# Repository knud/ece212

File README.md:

# ece212
decoder to 8x8 LED matrix

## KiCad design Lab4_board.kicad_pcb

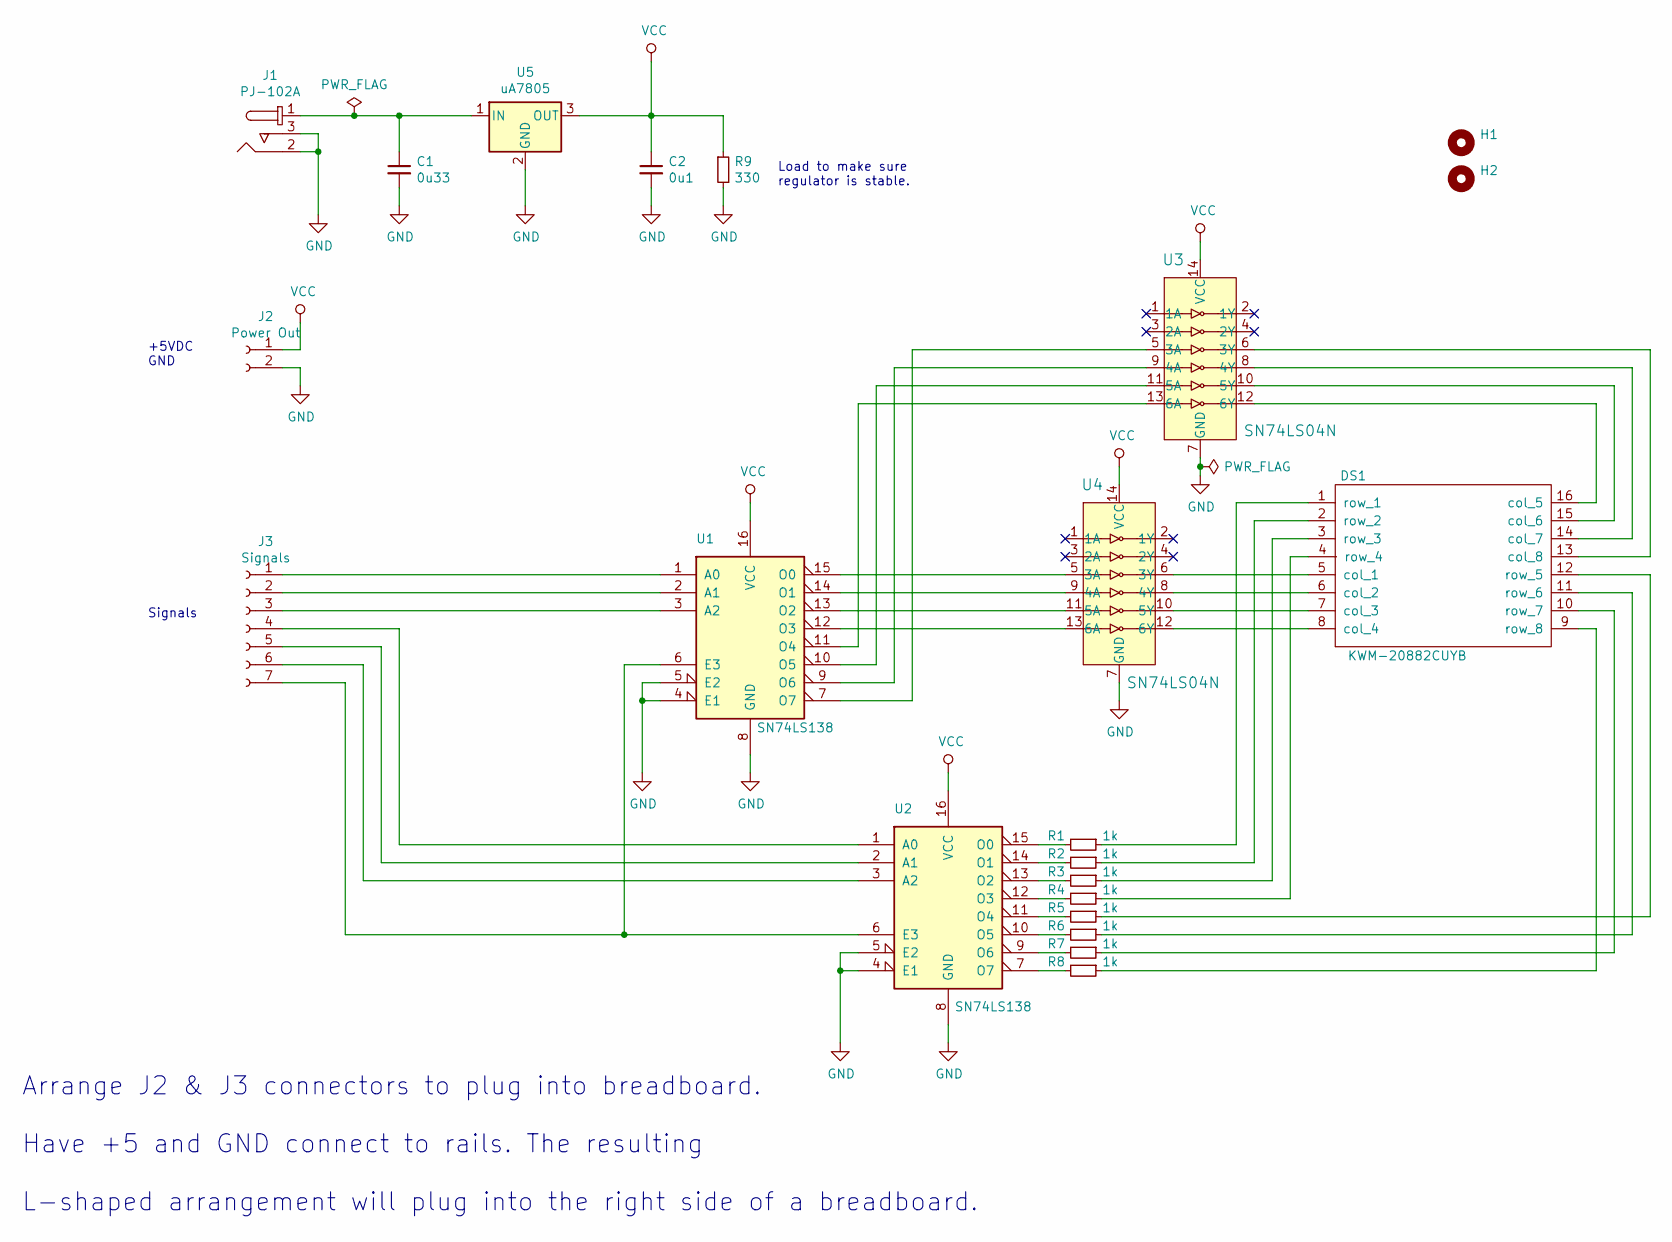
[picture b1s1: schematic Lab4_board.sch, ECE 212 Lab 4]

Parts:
C1: 0u33; C_0603; MPN CGA3E1X7R1V334K080AC
C2: 0u1; C_0603; MPN CL10A104KA8NNNC
DS1: KWM-20882CUYB; KWM-20882xxx
H1, H2: MountingHole_2.7mm_M2.5
J1: PJ-102A; Barrel_Jack_5.5mmODx2.1mmID_PJ-102A; MPN PJ-102A; Digi-Key_PN CP-102A-ND
J2: Power Out; Pin_Header_Straight_1x02_Pitch2.54mm
J3: Signals; Pin_Header_Straight_1x07_Pitch2.54mm
R1, R2, R3, R4, R5, R6, R7, R8: 1k; R_0603
R9: 330; R_0603; MPN RK73B1JTTD331J
U1, U2: SN74LS138; SOIC-16_W3.90mm
U3, U4: SN74LS04N; SOIC-14_W3.9mm; MPN SN74LS04DRE4; Digi-Key_PN SN74LS06DRE4-ND
U5: uA7805; T0263-3; MPN UA7805CKTTR

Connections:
GND: C1.2, C2.2, J1.2, J1.3, J2.2, R9.2, U1.4 (E1), U1.5 (E2), U1.8 (GND), U2.4 (E1), U2.5 (E2), U2.8 (GND), U3.7 (GND), U4.7 (GND), U5.2 (GND)
unnamed: C1.1, J1.1, U5.1 (IN)
unnamed: DS1.1 (row_1), R1.1
unnamed: DS1.2 (row_2), R2.1
unnamed: DS1.3 (row_3), R3.1
unnamed: DS1.4 (row_4), R4.1
unnamed: DS1.5 (col_1), U4.6 (3Y)
unnamed: DS1.6 (col_2), U4.8 (4Y)
unnamed: DS1.7 (col_3), U4.10 (5Y)
unnamed: DS1.8 (col_4), U4.12 (6Y)
unnamed: DS1.9 (row_8), R8.1
unnamed: DS1.10 (row_7), R7.1
unnamed: DS1.11 (row_6), R6.1
unnamed: DS1.12 (row_5), R5.1
unnamed: DS1.13 (col_8), U3.6 (3Y)
unnamed: DS1.14 (col_7), U3.8 (4Y)
unnamed: DS1.15 (col_6), U3.10 (5Y)
unnamed: DS1.16 (col_5), U3.12 (6Y)
unnamed: J3.1, U1.1 (A0)
unnamed: J3.2, U1.2 (A1)
unnamed: J3.3, U1.3 (A2)
unnamed: J3.4, U2.1 (A0)
unnamed: J3.5, U2.2 (A1)
unnamed: J3.6, U2.3 (A2)
unnamed: J3.7, U1.6 (E3), U2.6 (E3)
unnamed: R1.2, U2.15 (O0)
unnamed: R2.2, U2.14 (O1)
unnamed: R3.2, U2.13 (O2)
unnamed: R4.2, U2.12 (O3)
unnamed: R5.2, U2.11 (O4)
unnamed: R6.2, U2.10 (O5)
unnamed: R7.2, U2.9 (O6)
unnamed: R8.2, U2.7 (O7)
unnamed: U1.7 (O7), U3.5 (3A)
unnamed: U1.9 (O6), U3.9 (4A)
unnamed: U1.10 (O5), U3.11 (5A)
unnamed: U1.11 (O4), U3.13 (6A)
unnamed: U1.12 (O3), U4.13 (6A)
unnamed: U1.13 (O2), U4.11 (5A)
unnamed: U1.14 (O1), U4.9 (4A)
unnamed: U1.15 (O0), U4.5 (3A)
VCC: C2.1, J2.1, R9.1, U1.16 (VCC), U2.16 (VCC), U3.14 (VCC), U4.14 (VCC), U5.3 (OUT)

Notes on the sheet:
+5VDC GND
Signals
Arrange J2 & J3 connectors to plug into breadboard. Have +5 and GND connect to rails. The resulting L-shaped arrangement will plug into the right side of a breadboard.
Load to make sure regulator is stable.

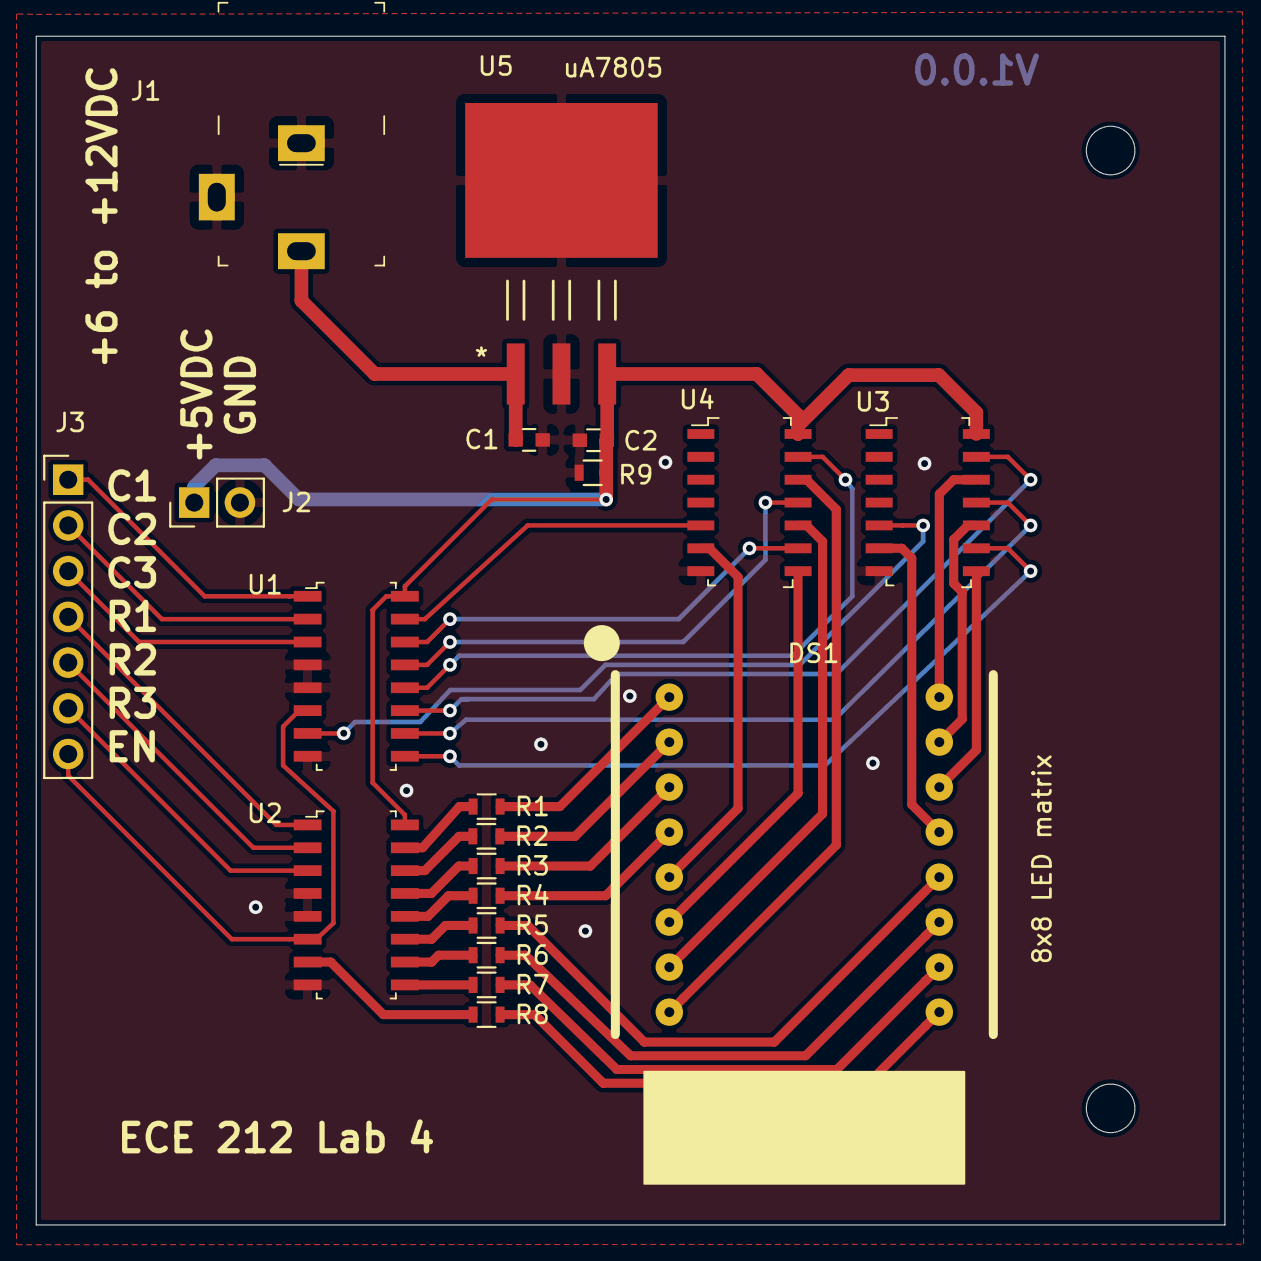
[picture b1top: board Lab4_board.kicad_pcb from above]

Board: 2 copper layers, 66.0 x 66.0 mm, 22 parts (0 on the bottom side), 42 nets.

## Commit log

2020-07-22 final version for 20882 matrix

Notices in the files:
Lab4_board.kicad_pcb:
License : CC BY 4.0
© ECE Department
Lab4_board.sch:
https://creativecommons.org/licenses/by/4.0
parts and their libraries:
Copyright 2016 Accelerated Designs. All rights reserved.
